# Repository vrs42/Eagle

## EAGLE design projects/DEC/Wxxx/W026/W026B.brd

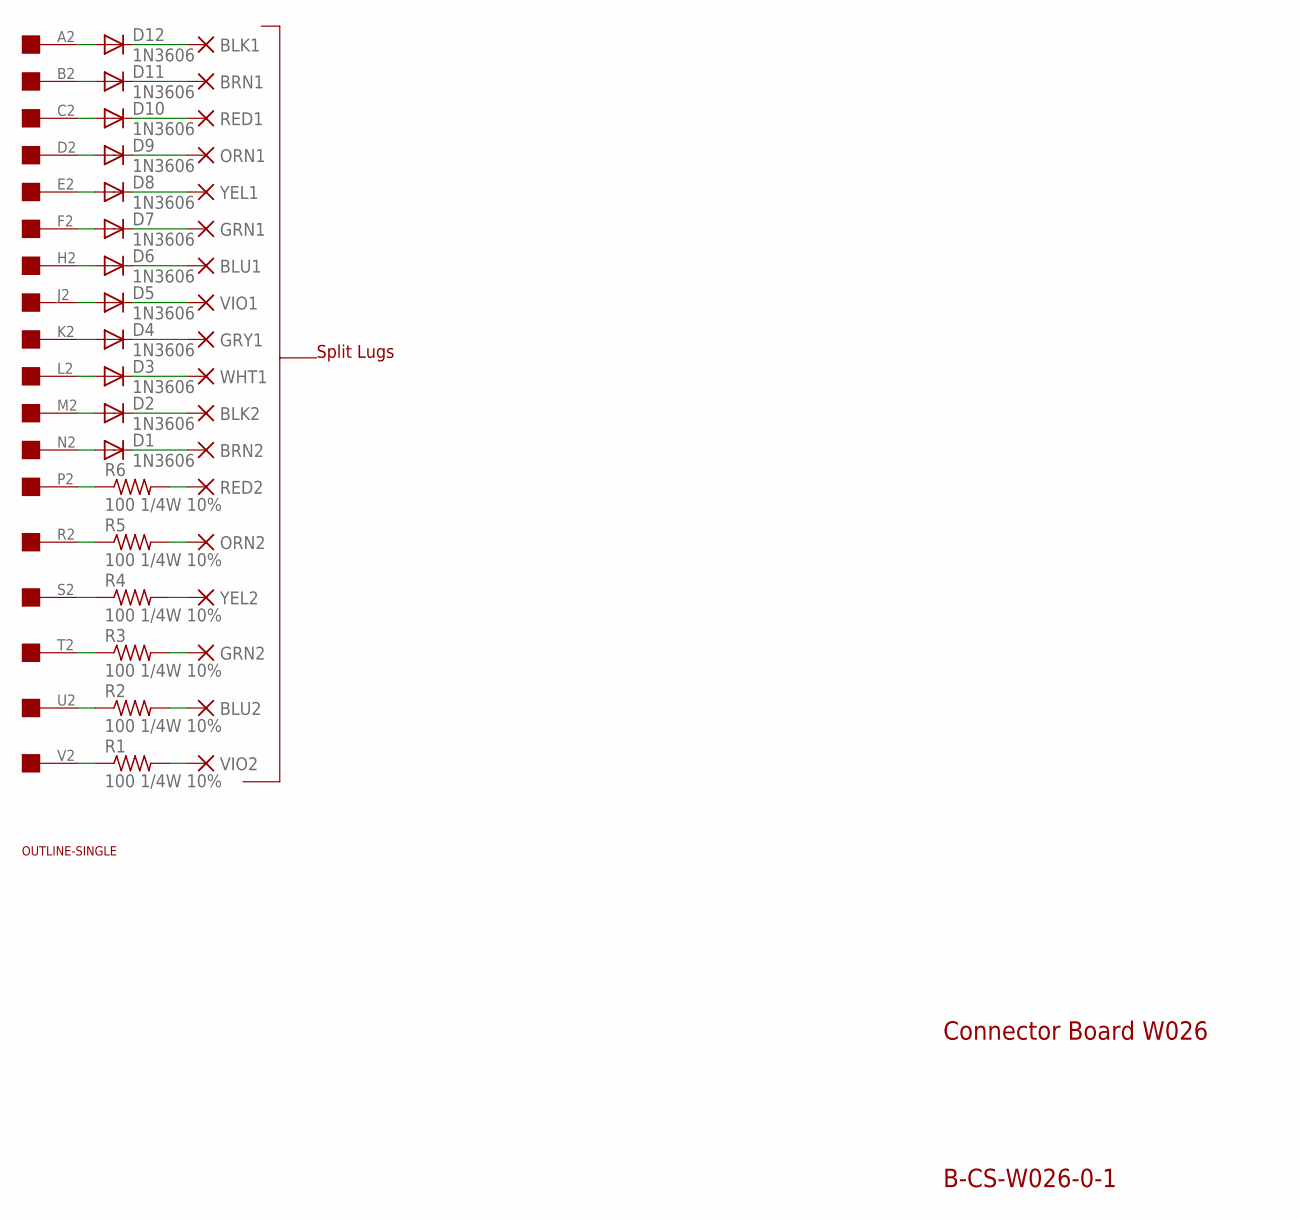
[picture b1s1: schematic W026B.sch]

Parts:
BLK1, BLK2: PAD-0465; 0465
BLU1, BLU2: PAD-0465; 0465
BRN1, BRN2: PAD-0465; 0465
D1, D2, D3, D4, D5, D6, D7, D8, D9, D10, D11, D12: 1N3606; DO35-10
GRN1, GRN2: PAD-0465; 0465
GRY1: PAD-0465; 0465
ORN1, ORN2: PAD-0465; 0465
R1, R2, R3, R4, R5, R6: 100 1/4W 10%; 0207/10
RED1, RED2: PAD-0465; 0465
U$1: OUTLINE-SINGLE; SINGLE
U$2: EDGE-1; EDGE-CON1
VIO1, VIO2: PAD-0465; 0465
WHT1: PAD-0465; 0465
YEL1, YEL2: PAD-0465; 0465

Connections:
unnamed: D10.C, RED1.P$1
unnamed: D7.C, GRN1.P$1
unnamed: D5.C, VIO1.P$1
unnamed: D3.C, WHT1.P$1
unnamed: BRN2.P$1, D1.C
unnamed: ORN2.P$1, R5.2
unnamed: GRN2.P$1, R3.2
unnamed: R1.2, VIO2.P$1
unnamed: BRN1.P$1, D11.C
unnamed: BLK1.P$1, D12.C
unnamed: D1.A, U$2.N2
unnamed: D8.C, YEL1.P$1
unnamed: BLU1.P$1, D6.C
unnamed: D4.C, GRY1.P$1
unnamed: D9.C, ORN1.P$1
unnamed: BLU2.P$1, R2.2
unnamed: R4.2, YEL2.P$1
unnamed: R6.2, RED2.P$1
unnamed: BLK2.P$1, D2.C
unnamed: D11.A, U$2.B2
unnamed: D12.A, U$2.A2
unnamed: D2.A, U$2.M2
unnamed: D3.A, U$2.L2
unnamed: D4.A, U$2.K2
unnamed: D5.A, U$2.J2
unnamed: D6.A, U$2.H2
unnamed: D7.A, U$2.F2
unnamed: D8.A, U$2.E2
unnamed: D9.A, U$2.D2
unnamed: D10.A, U$2.C2
unnamed: R6.1, U$2.P2
unnamed: R1.1, U$2.V2
unnamed: R2.1, U$2.U2
unnamed: R3.1, U$2.T2
unnamed: R4.1, U$2.S2
unnamed: R5.1, U$2.R2

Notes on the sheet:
Connector Board W026
B-CS-W026-0-1
Split Lugs

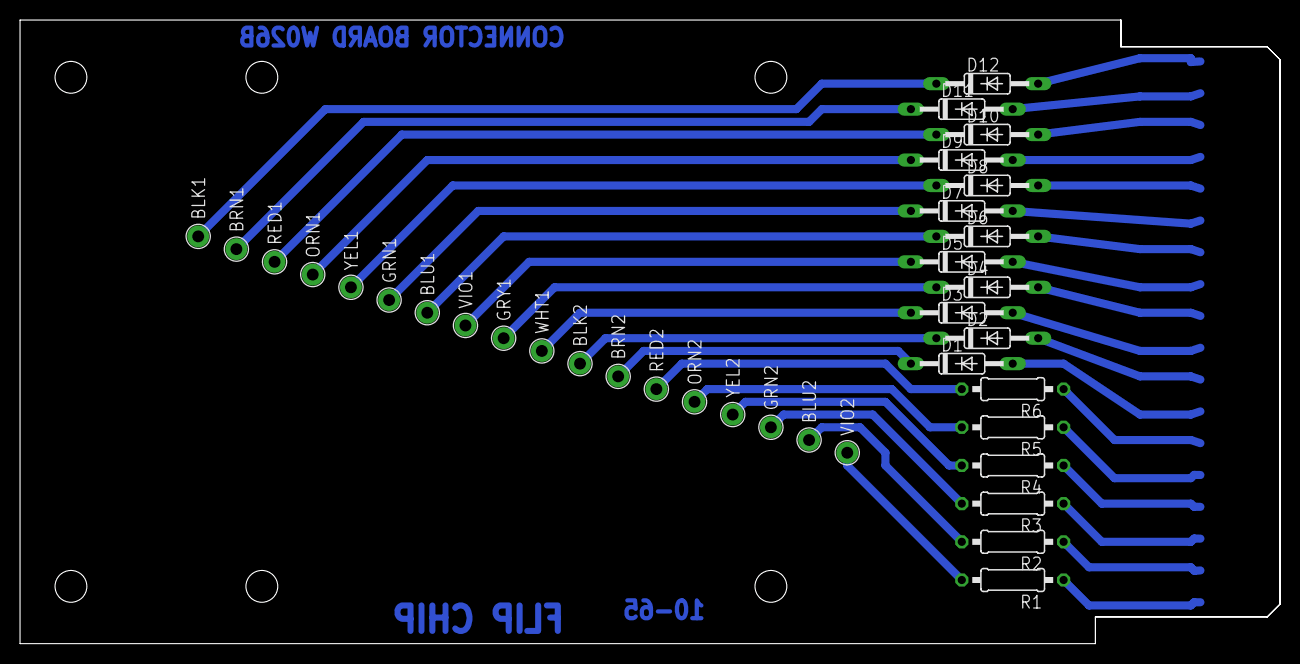
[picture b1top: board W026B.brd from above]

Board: 2 copper layers, 125.7 x 62.2 mm, 38 parts (0 on the bottom side), 36 nets.

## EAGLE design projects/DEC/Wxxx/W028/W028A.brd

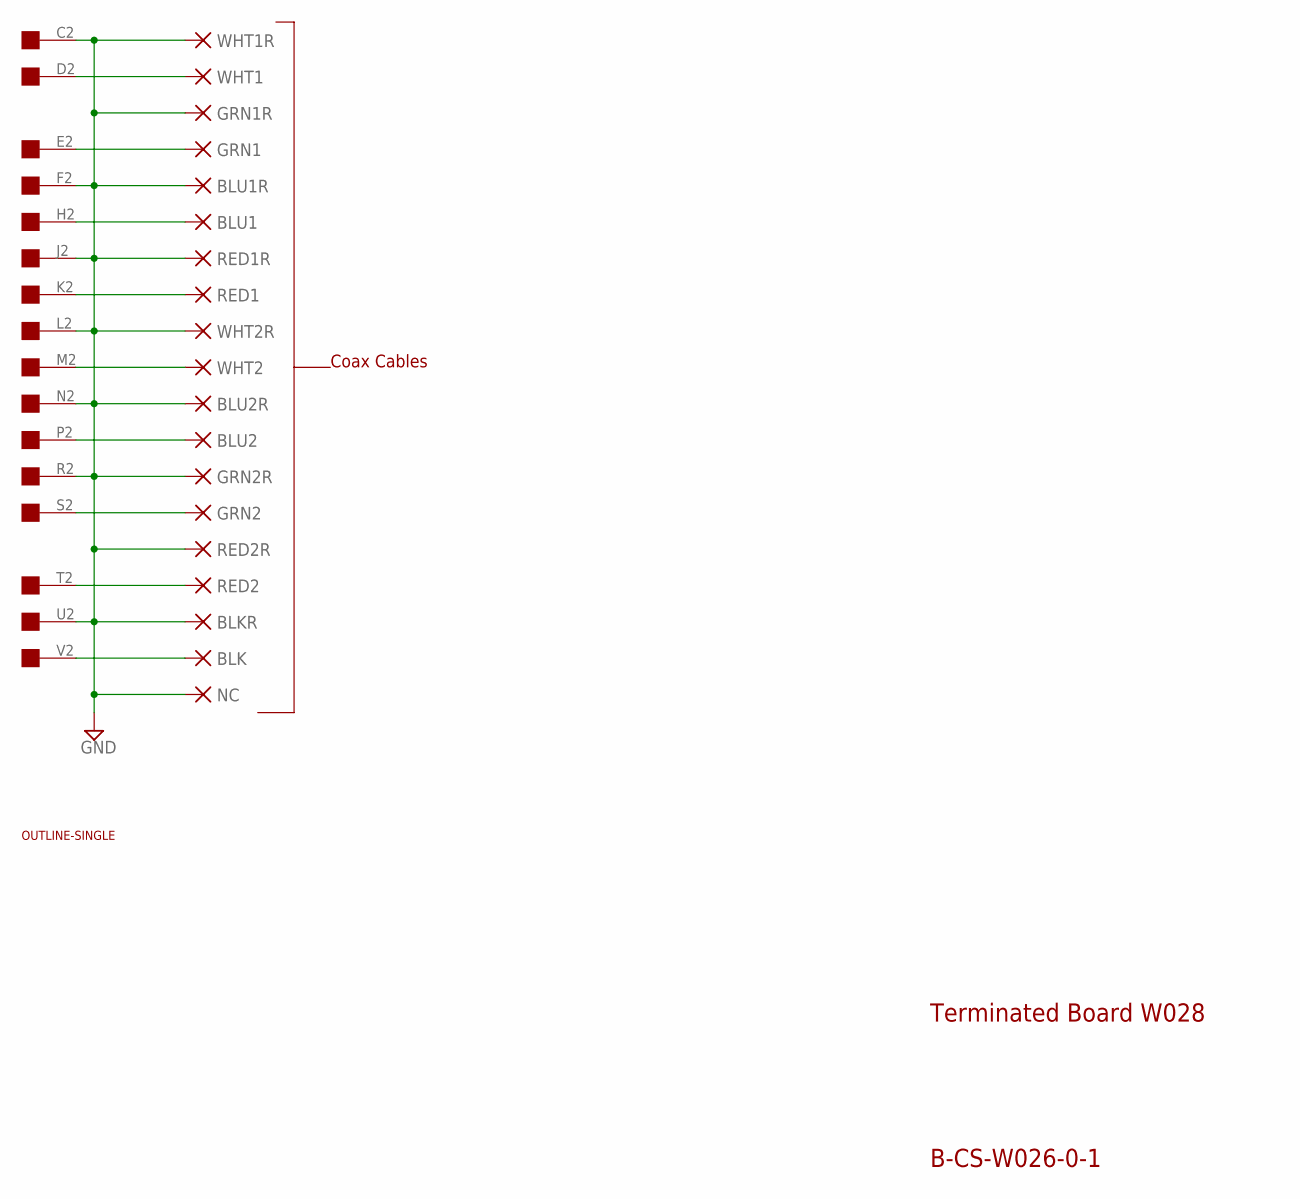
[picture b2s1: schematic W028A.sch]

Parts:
BLK: PAD-0465; 0465
BLKR: PAD-0465; 0465
BLU1, BLU1R, BLU2, BLU2R: PAD-0465; 0465
GRN1, GRN1R, GRN2, GRN2R: PAD-0465; 0465
NC: PAD-0465; 0465
RED1, RED1R, RED2, RED2R: PAD-0465; 0465
U$1: OUTLINE-SINGLE; SINGLE
U$2: EDGE-1; EDGE-CON1
WHT1, WHT1R, WHT2, WHT2R: PAD-0465; 0465

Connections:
GND: BLKR.P$1, BLU1R.P$1, BLU2R.P$1, GRN1R.P$1, GRN2R.P$1, NC.P$1, RED1R.P$1, RED2R.P$1, U$2.C2, U$2.F2, U$2.J2, U$2.L2, U$2.N2, U$2.R2, U$2.U2, WHT1R.P$1, WHT2R.P$1
unnamed: GRN1.P$1, U$2.E2
unnamed: BLU1.P$1, U$2.H2
unnamed: RED1.P$1, U$2.K2
unnamed: U$2.M2, WHT2.P$1
unnamed: BLU2.P$1, U$2.P2
unnamed: GRN2.P$1, U$2.S2
unnamed: RED2.P$1, U$2.T2
unnamed: BLK.P$1, U$2.V2
unnamed: U$2.D2, WHT1.P$1

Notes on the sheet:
Terminated Board W028
B-CS-W026-0-1
Coax Cables

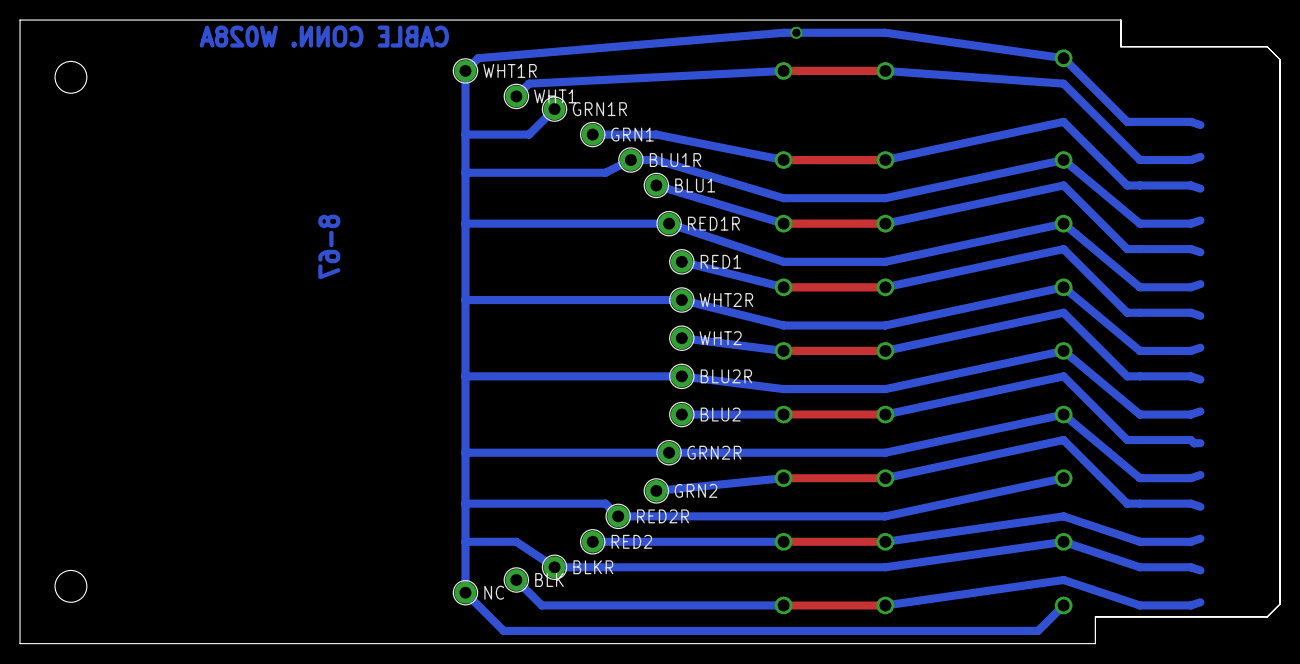
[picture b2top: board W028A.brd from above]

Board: 2 copper layers, 125.7 x 62.2 mm, 21 parts (0 on the bottom side), 10 nets.

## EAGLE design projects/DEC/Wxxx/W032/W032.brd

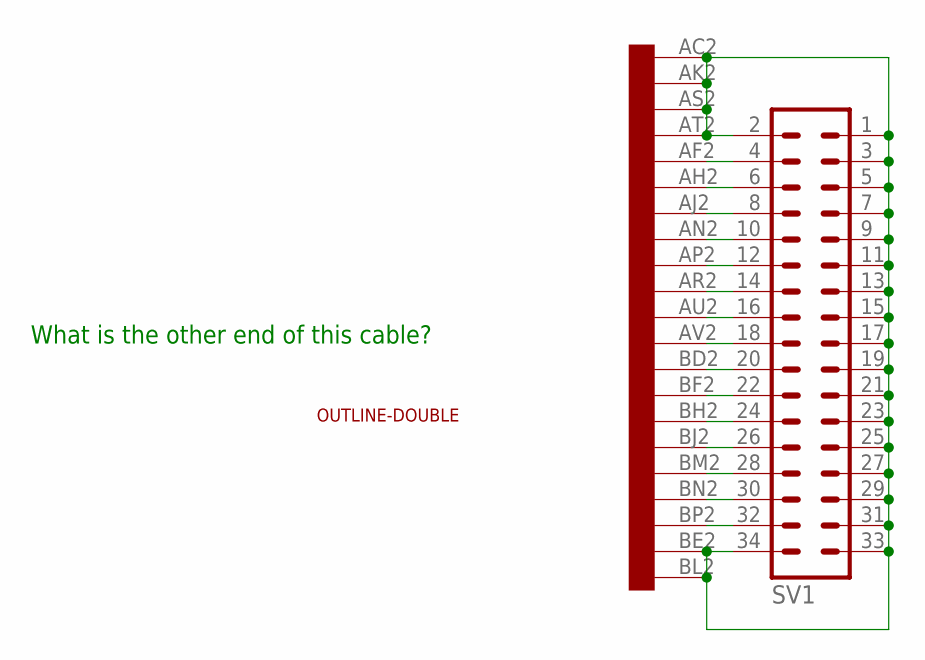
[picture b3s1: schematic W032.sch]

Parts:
SV1: MA17-2
U$1: OUTLINE-DOUBLE; DOUBLE
U$2: DOUBLE; EDGE-CON4

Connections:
GND: SV1.1, SV1.2, SV1.3, SV1.5, SV1.7, SV1.9, SV1.11, SV1.13, SV1.15, SV1.17, SV1.19, SV1.21, SV1.23, SV1.25, SV1.27, SV1.29, SV1.31, SV1.33, SV1.34, U$2.AC2, U$2.AK2, U$2.AS2, U$2.AT2, U$2.BE2, U$2.BL2
unnamed: SV1.4, U$2.AF2
unnamed: SV1.6, U$2.AH2
unnamed: SV1.8, U$2.AJ2
unnamed: SV1.10, U$2.AN2
unnamed: SV1.12, U$2.AP2
unnamed: SV1.14, U$2.AR2
unnamed: SV1.16, U$2.AU2
unnamed: SV1.18, U$2.AV2
unnamed: SV1.20, U$2.BD2
unnamed: SV1.22, U$2.BF2
unnamed: SV1.24, U$2.BH2
unnamed: SV1.26, U$2.BJ2
unnamed: SV1.28, U$2.BM2
unnamed: SV1.30, U$2.BN2
unnamed: SV1.32, U$2.BP2

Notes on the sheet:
What is the other end of this cable?

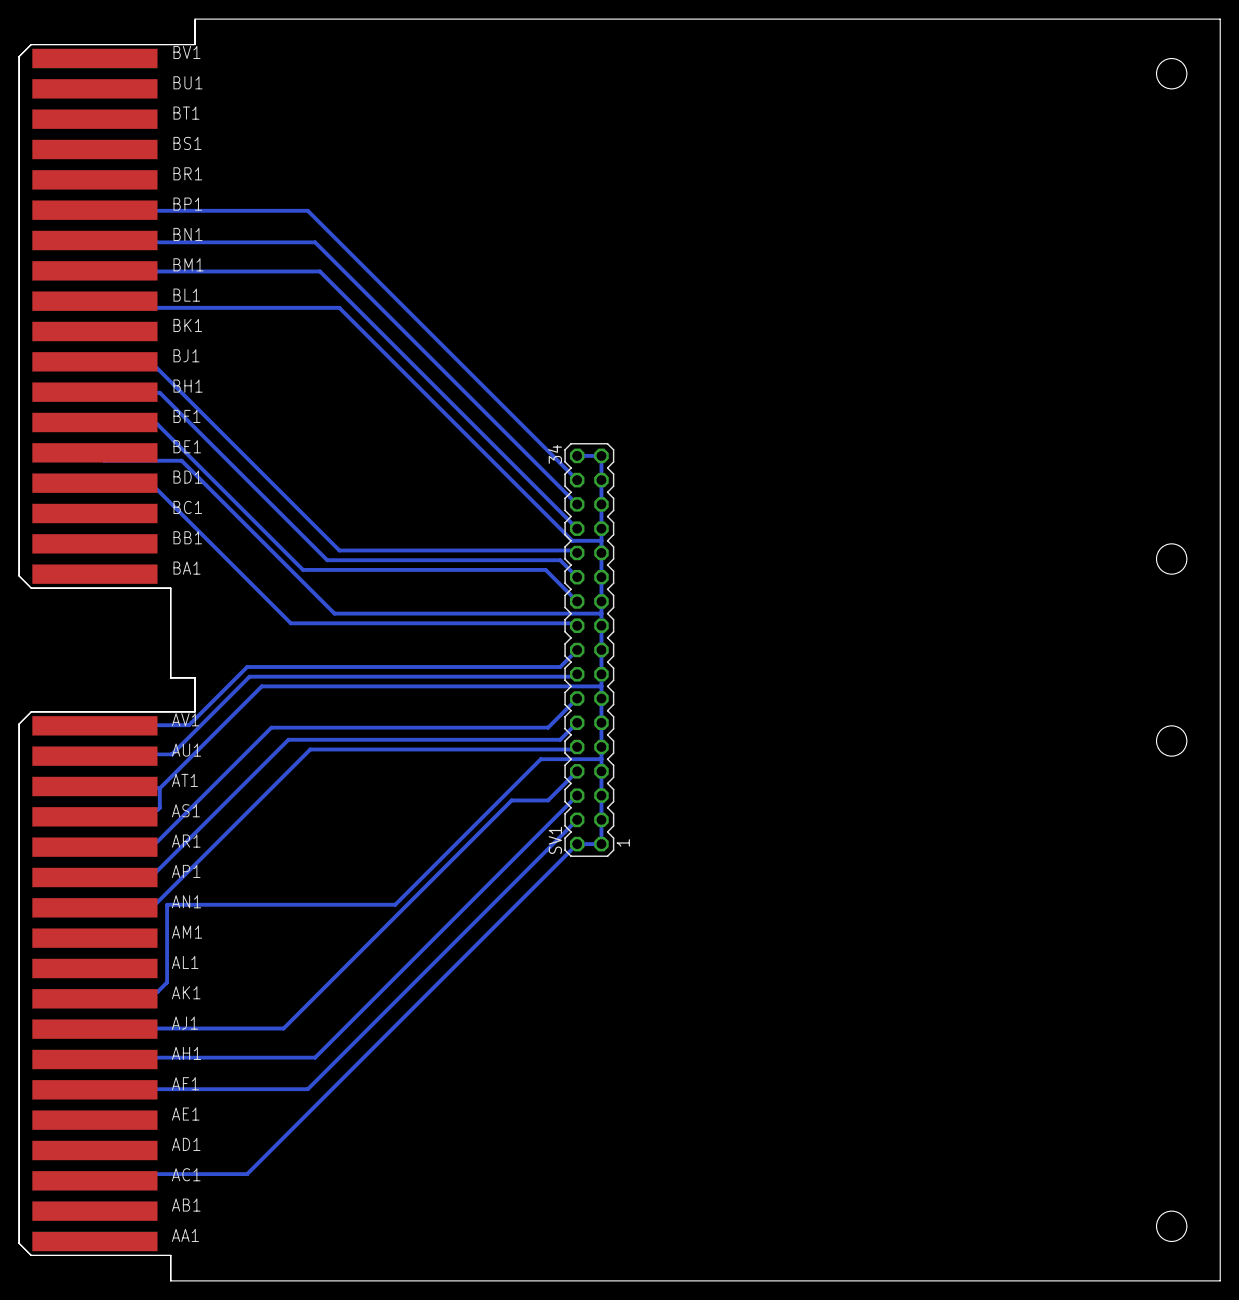
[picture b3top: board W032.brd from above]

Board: 2 copper layers, 125.7 x 132.1 mm, 3 parts (0 on the bottom side), 16 nets.

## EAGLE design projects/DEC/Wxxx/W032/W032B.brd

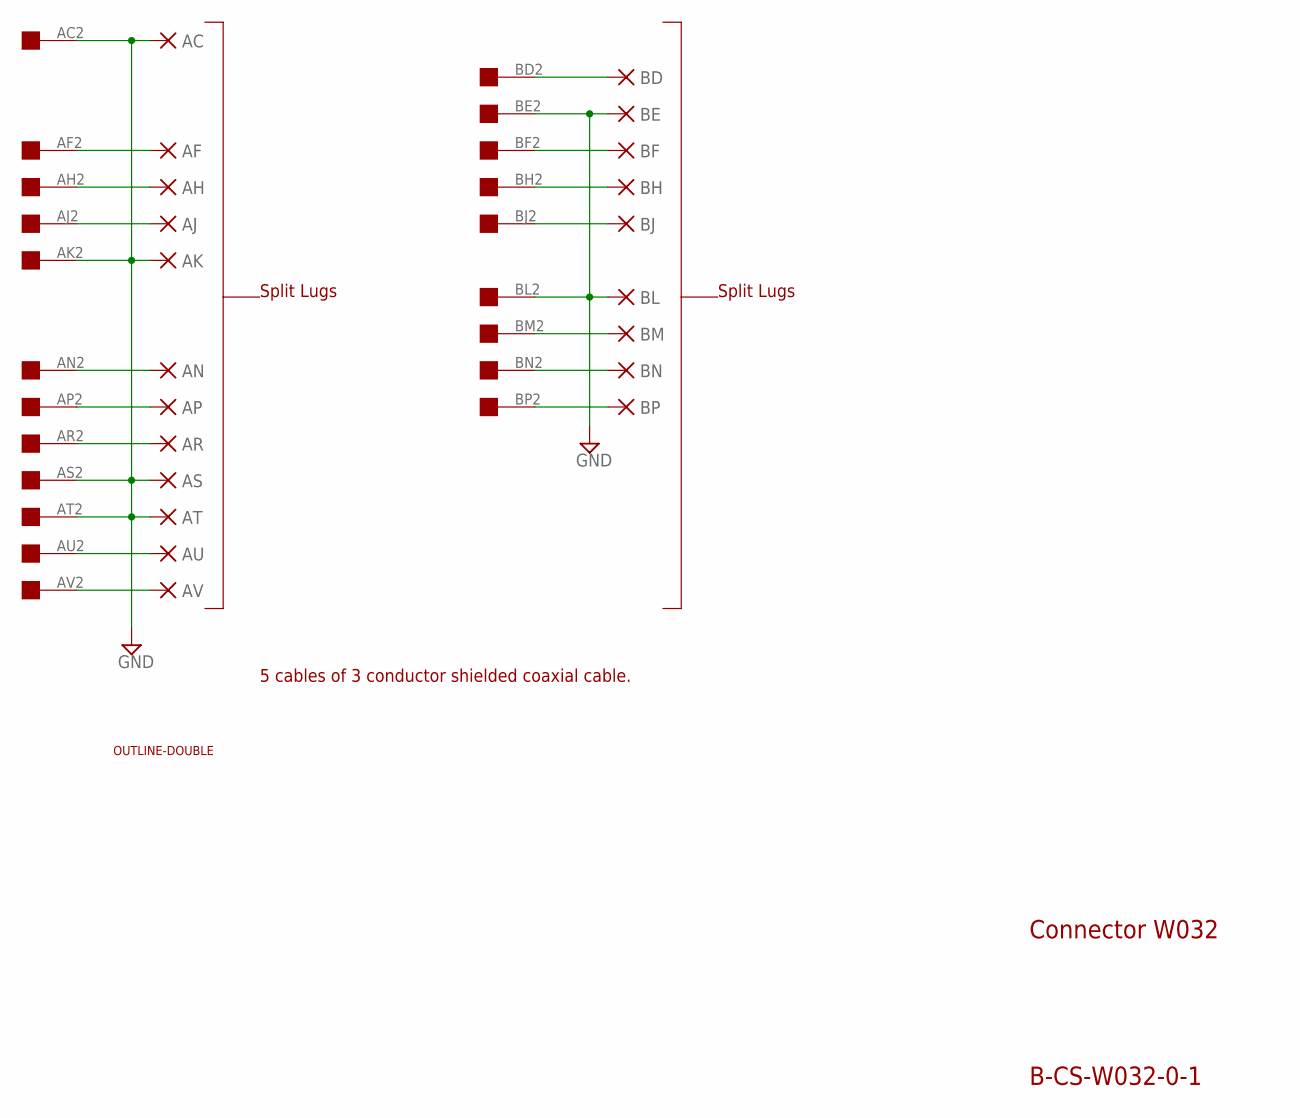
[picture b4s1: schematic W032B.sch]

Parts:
AC: PAD-0465; 0465
AF: PAD-0465; 0465
AH: PAD-0465; 0465
AJ: PAD-0465; 0465
AK: PAD-0465; 0465
AN: PAD-0465; 0465
AP: PAD-0465; 0465
AR: PAD-0465; 0465
AS: PAD-0465; 0465
AT: PAD-0465; 0465
AU: PAD-0465; 0465
AV: PAD-0465; 0465
BD: PAD-0465; 0465
BE: PAD-0465; 0465
BF: PAD-0465; 0465
BH: PAD-0465; 0465
BJ: PAD-0465; 0465
BL: PAD-0465; 0465
BM: PAD-0465; 0465
BN: PAD-0465; 0465
BP: PAD-0465; 0465
U$1: OUTLINE-DOUBLE; DOUBLE
U$3: DOUBLE; EDGE-CON4

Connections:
GND: AC.P$1, AK.P$1, AS.P$1, AT.P$1, BE.P$1, BL.P$1, U$3.AC2, U$3.AK2, U$3.AS2, U$3.AT2, U$3.BE2, U$3.BL2
unnamed: BH.P$1, U$3.BH2
unnamed: BM.P$1, U$3.BM2
unnamed: BP.P$1, U$3.BP2
unnamed: BD.P$1, U$3.BD2
unnamed: AH.P$1, U$3.AH2
unnamed: BF.P$1, U$3.BF2
unnamed: BJ.P$1, U$3.BJ2
unnamed: BN.P$1, U$3.BN2
unnamed: AP.P$1, U$3.AP2
unnamed: AF.P$1, U$3.AF2
unnamed: AJ.P$1, U$3.AJ2
unnamed: AN.P$1, U$3.AN2
unnamed: AR.P$1, U$3.AR2
unnamed: AU.P$1, U$3.AU2
unnamed: AV.P$1, U$3.AV2

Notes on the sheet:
Connector W032
B-CS-W032-0-1
Split Lugs
5 cables of 3 conductor shielded coaxial cable.

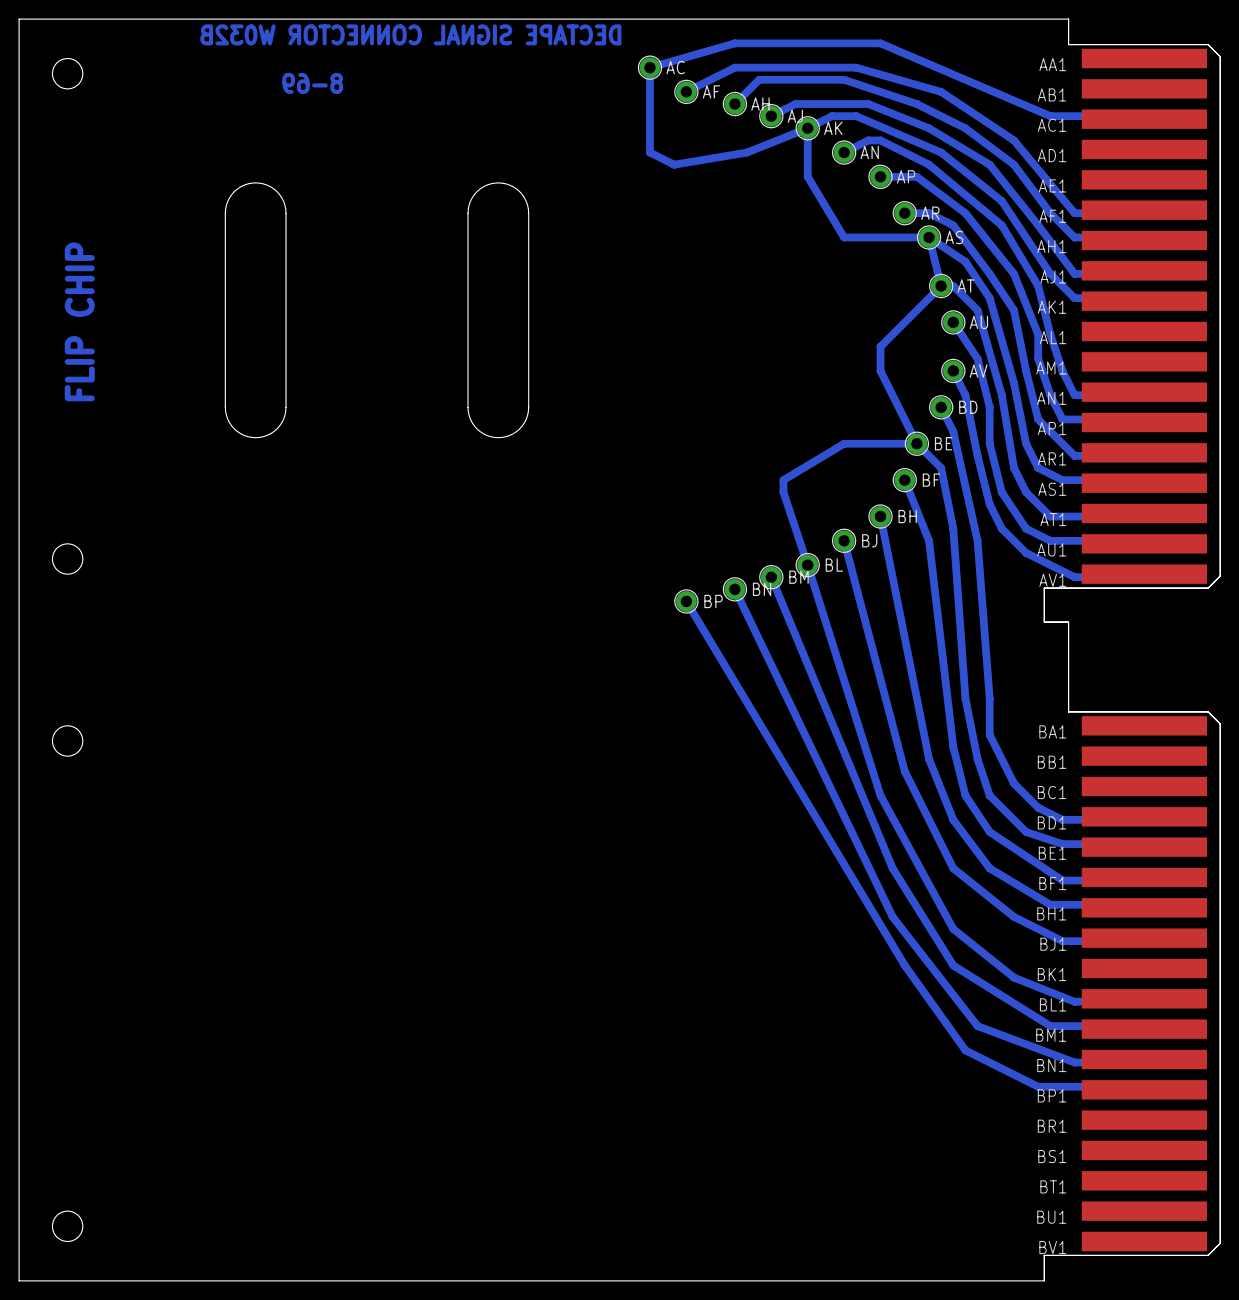
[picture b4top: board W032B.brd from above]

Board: 2 copper layers, 125.7 x 132.1 mm, 23 parts (0 on the bottom side), 16 nets.

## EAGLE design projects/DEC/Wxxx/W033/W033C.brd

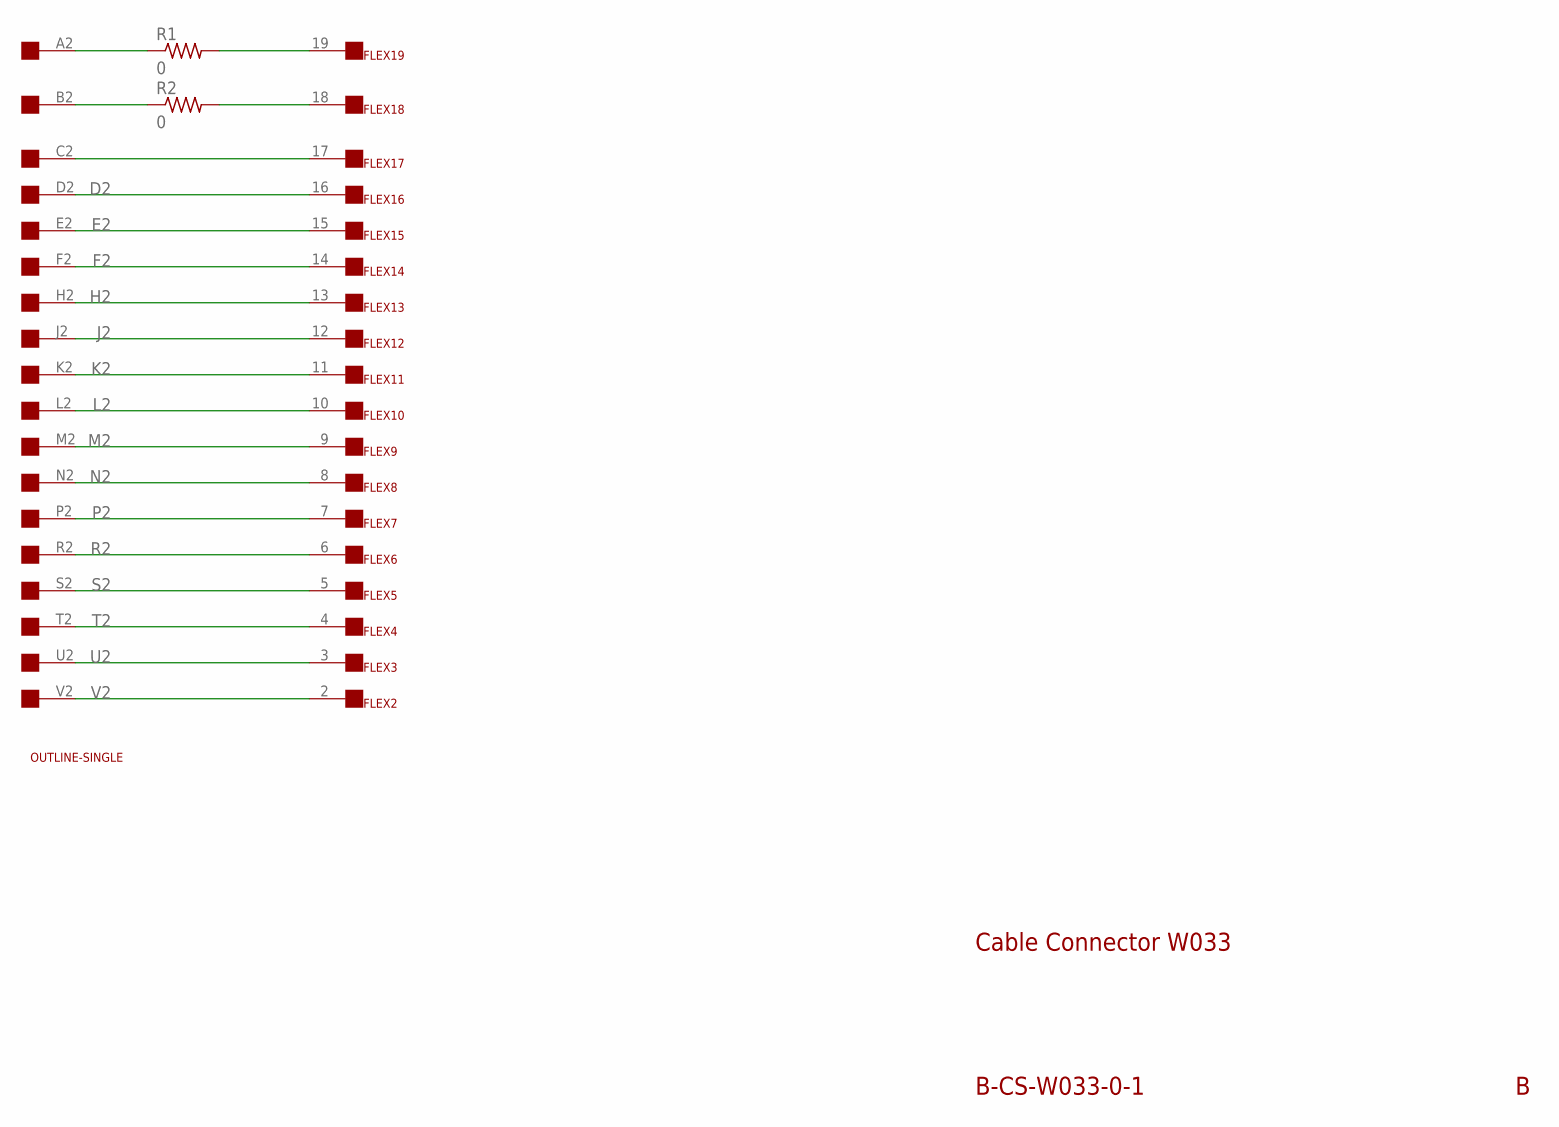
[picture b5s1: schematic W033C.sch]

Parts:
FLEX: FLEX19
R1, R2: 0; 0207/10
U$1: OUTLINE-SINGLE; SINGLE
U$2: EDGE-1; EDGE-CON1

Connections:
B2: R2.1, U$2.B2
D2: FLEX.16, U$2.D2
E2: FLEX.15, U$2.E2
F2: FLEX.14, U$2.F2
H2: FLEX.13, U$2.H2
J2: FLEX.12, U$2.J2
K2: FLEX.11, U$2.K2
L2: FLEX.10, U$2.L2
M2: FLEX.9, U$2.M2
N2: FLEX.8, U$2.N2
unnamed: FLEX.17, U$2.C2
unnamed: R1.1, U$2.A2
unnamed: FLEX.19, R1.2
unnamed: FLEX.18, R2.2
P2: FLEX.7, U$2.P2
R2: FLEX.6, U$2.R2
S2: FLEX.5, U$2.S2
T2: FLEX.4, U$2.T2
U2: FLEX.3, U$2.U2
V2: FLEX.2, U$2.V2

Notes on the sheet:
B-CS-W033-0-1
Cable Connector W033

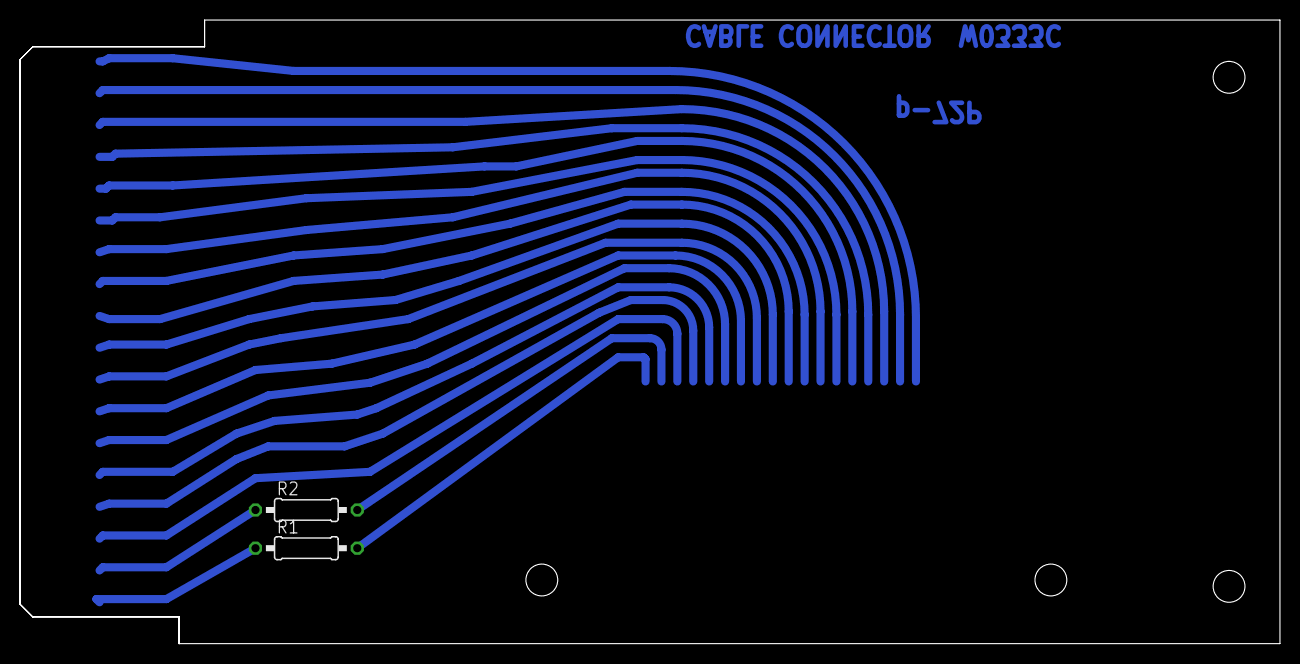
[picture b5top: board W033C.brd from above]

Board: 2 copper layers, 125.7 x 62.2 mm, 5 parts (1 on the bottom side), 20 nets.
